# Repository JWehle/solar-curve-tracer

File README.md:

# solar-curve-tracer
Full solar cell characterization, IV curve, and irradiance.

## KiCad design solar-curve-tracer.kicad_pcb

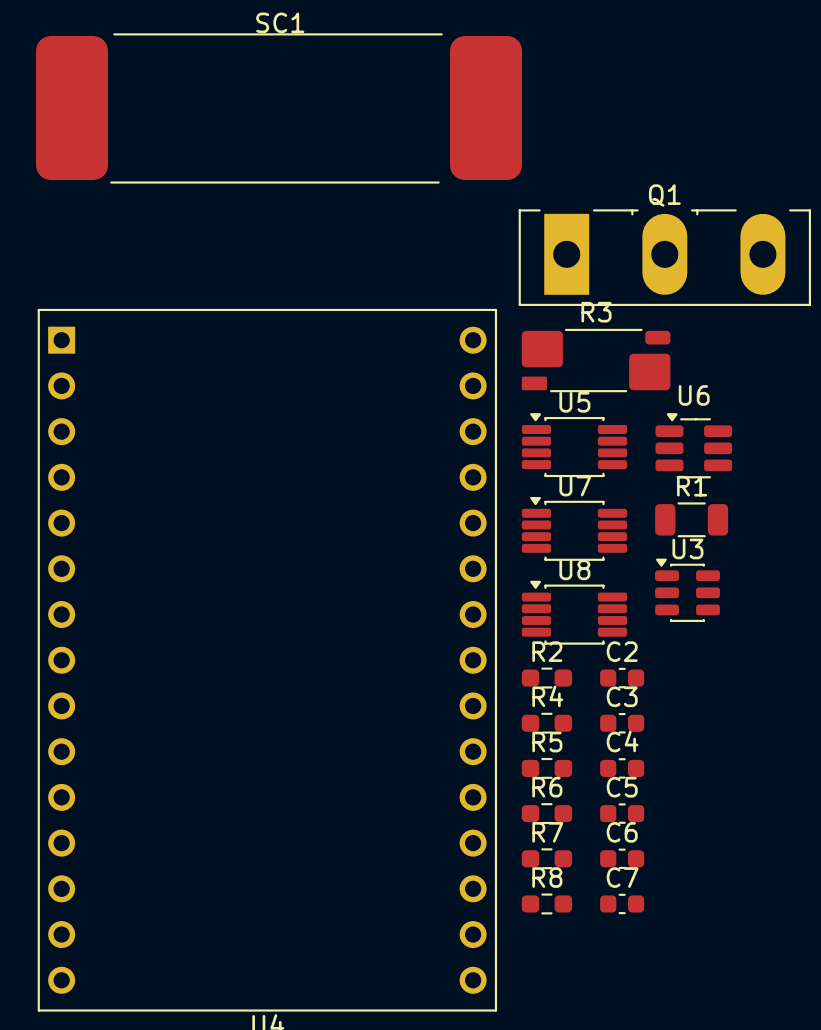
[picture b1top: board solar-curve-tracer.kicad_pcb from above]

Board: 2 copper layers, 22 parts (0 on the bottom side), 16 nets, no tracks yet.

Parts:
C2, C3, C4, C5, C6: 0.1uF; C_0603_1608Metric
C7: 56pF; C_0603_1608Metric
Q1: IXTH64N10L2; TO-247-3_Vertical
R1: 0.5; R_1206_3216Metric
R2: 47; R_0603_1608Metric_Pad0.98x0.95mm_HandSolder
R3: 1m; R_Shunt_Vishay_WSK2512_6332Metric_T1.19mm
R4, R5: 1K; R_0603_1608Metric_Pad0.98x0.95mm_HandSolder
R6, R7, R8: 15K; R_0603_1608Metric_Pad0.98x0.95mm_HandSolder
SC1: KXOB25-14X1F-TR
U3: LM2665M6; SOT-23-6
U4: ESP32-C3-DevKitM-1
U5, U7, U8: TMP1075DGK; VSSOP-8_3x3mm_P0.65mm
U6: MAX5812MEUT+T; SOT-23-6_Handsoldering

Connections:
+3.3V: C2.1, C3.1, C4.1, C5.1, C6.1, R6.2, U5.8 (V+), U6.1 (VDD), U7.8 (V+), U8.8 (V+)
/SCL: U5.2 (SCL), U6.4 (SCL), U7.2 (SCL), U8.2 (SCL)
/SDA: U5.1 (SDA), U6.3 (SDA), U7.1 (SDA), U8.1 (SDA)
GND: C2.2, C3.2, C4.2, C5.2, C6.2, R1.2, R3.4, R8.1, SC1.2 (-), U3.2 (GND_2), U4.1 (GND), U4.6 (GND), U4.8 (GND), U4.12 (GND), U4.15 (GND), U4.16 (GND), U4.19 (GND), U4.24 (GND), U4.27 (GND), U4.30 (GND), U5.4 (GND), U6.2 (VSS), U7.4 (GND), U8.4 (GND)
unnamed: C7.1, R2.1
unnamed: Q1.1 (G), R2.2
unnamed: Q1.3 (S), R3.1
unnamed: R3.2, R4.2
unnamed: R3.3, R5.2
unnamed: R1.1, SC1.1 (+)
unnamed: R5.1, R7.2
unnamed: C7.2, R4.1, R8.2
unnamed: U4.2 (3V3), U4.3 (3V3)
unnamed: U4.13 (5V), U4.14 (5V)
unnamed: R7.1, U6.6 (VOUT)
unnamed: R6.1, U8.3 (ALERT)

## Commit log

2026-04-11 schematic
